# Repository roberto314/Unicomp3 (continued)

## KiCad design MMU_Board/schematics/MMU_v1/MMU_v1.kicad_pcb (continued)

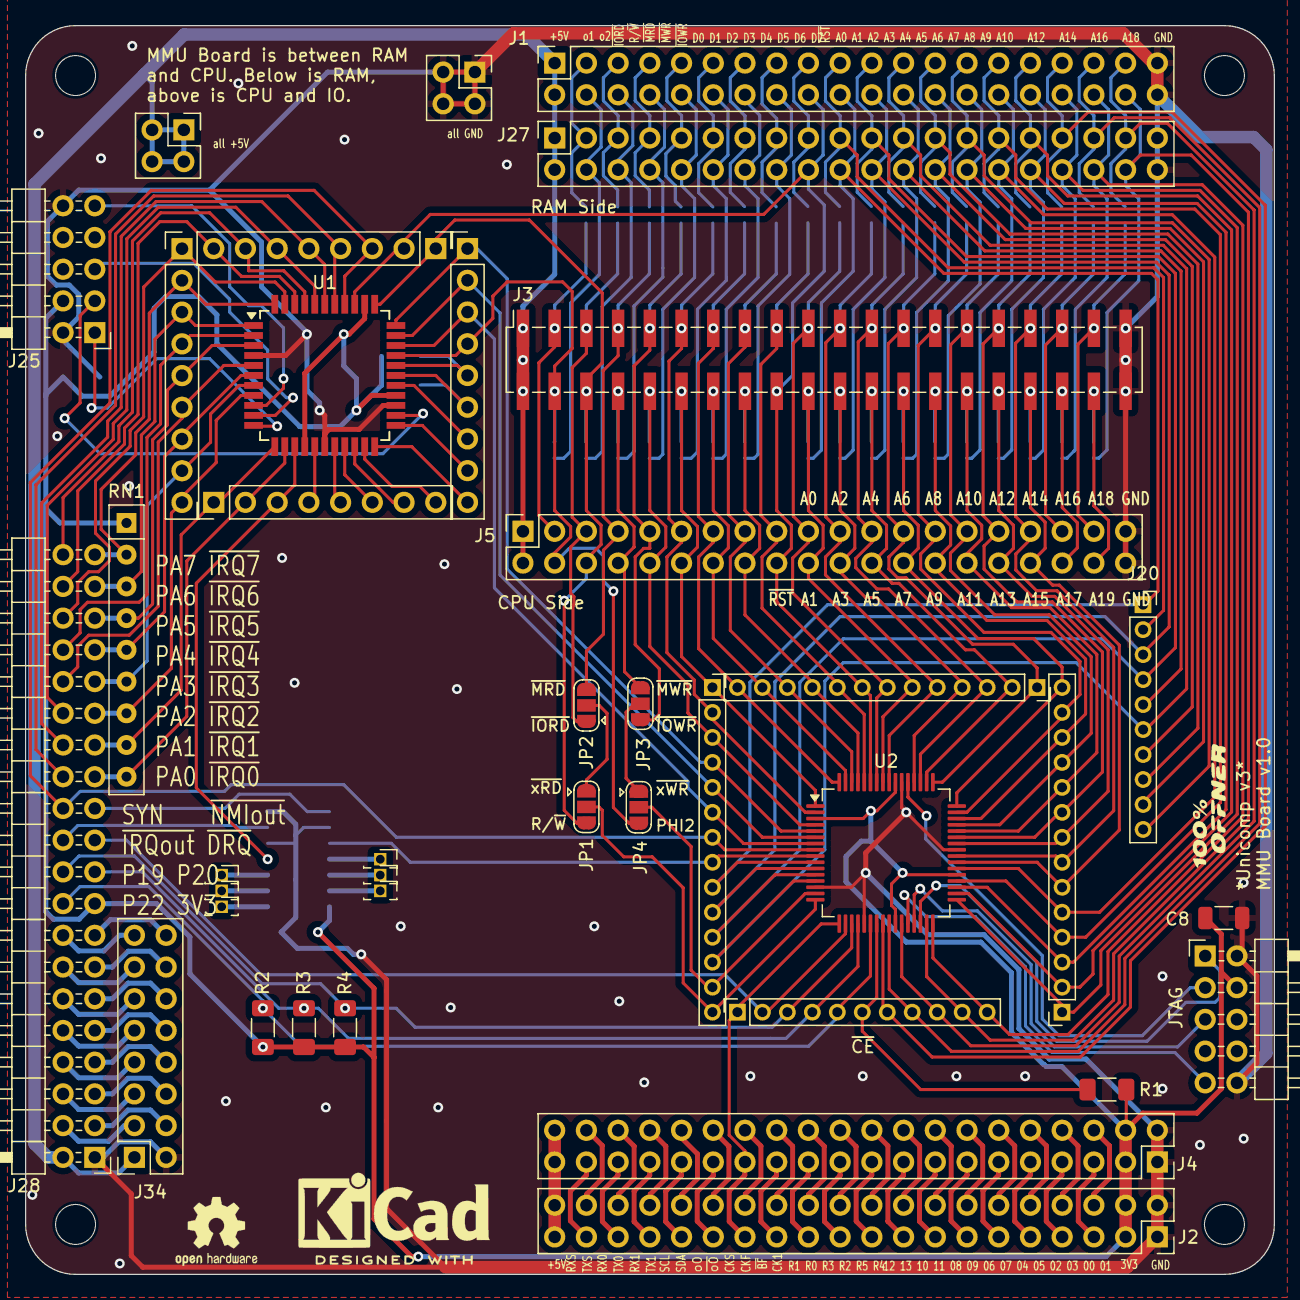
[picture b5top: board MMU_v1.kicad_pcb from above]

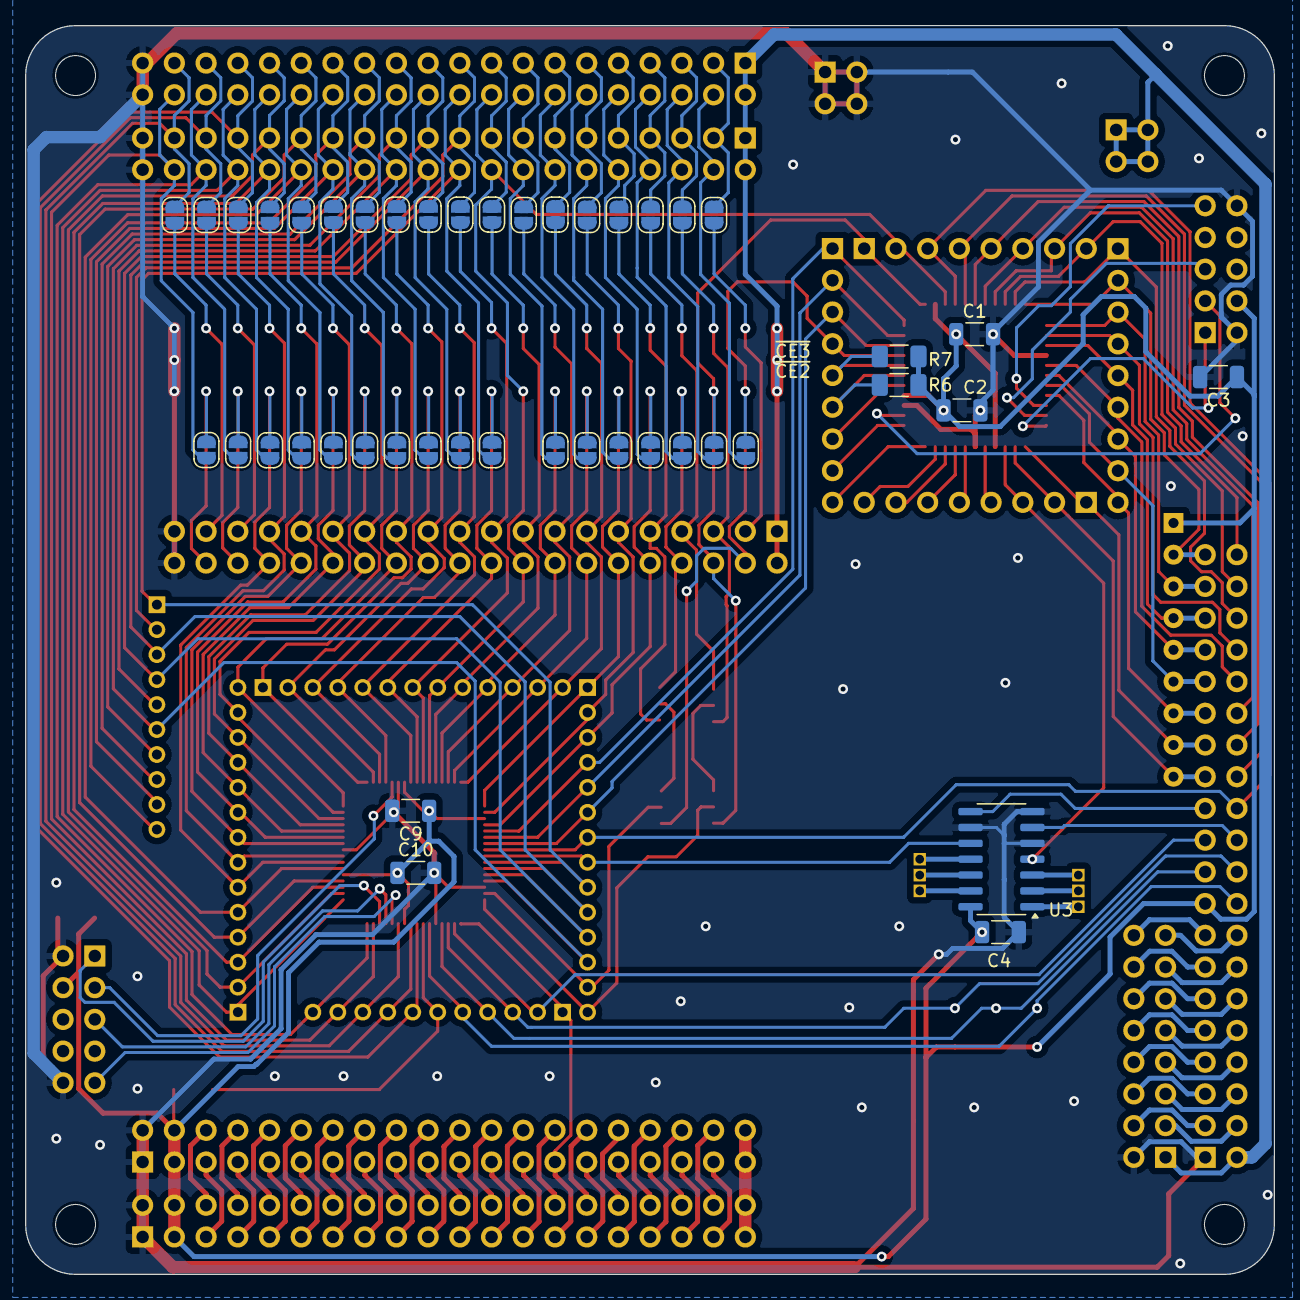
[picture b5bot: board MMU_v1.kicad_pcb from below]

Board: 2 copper layers, 100.0 x 100.0 mm, 89 parts (44 on the bottom side), 180 nets.

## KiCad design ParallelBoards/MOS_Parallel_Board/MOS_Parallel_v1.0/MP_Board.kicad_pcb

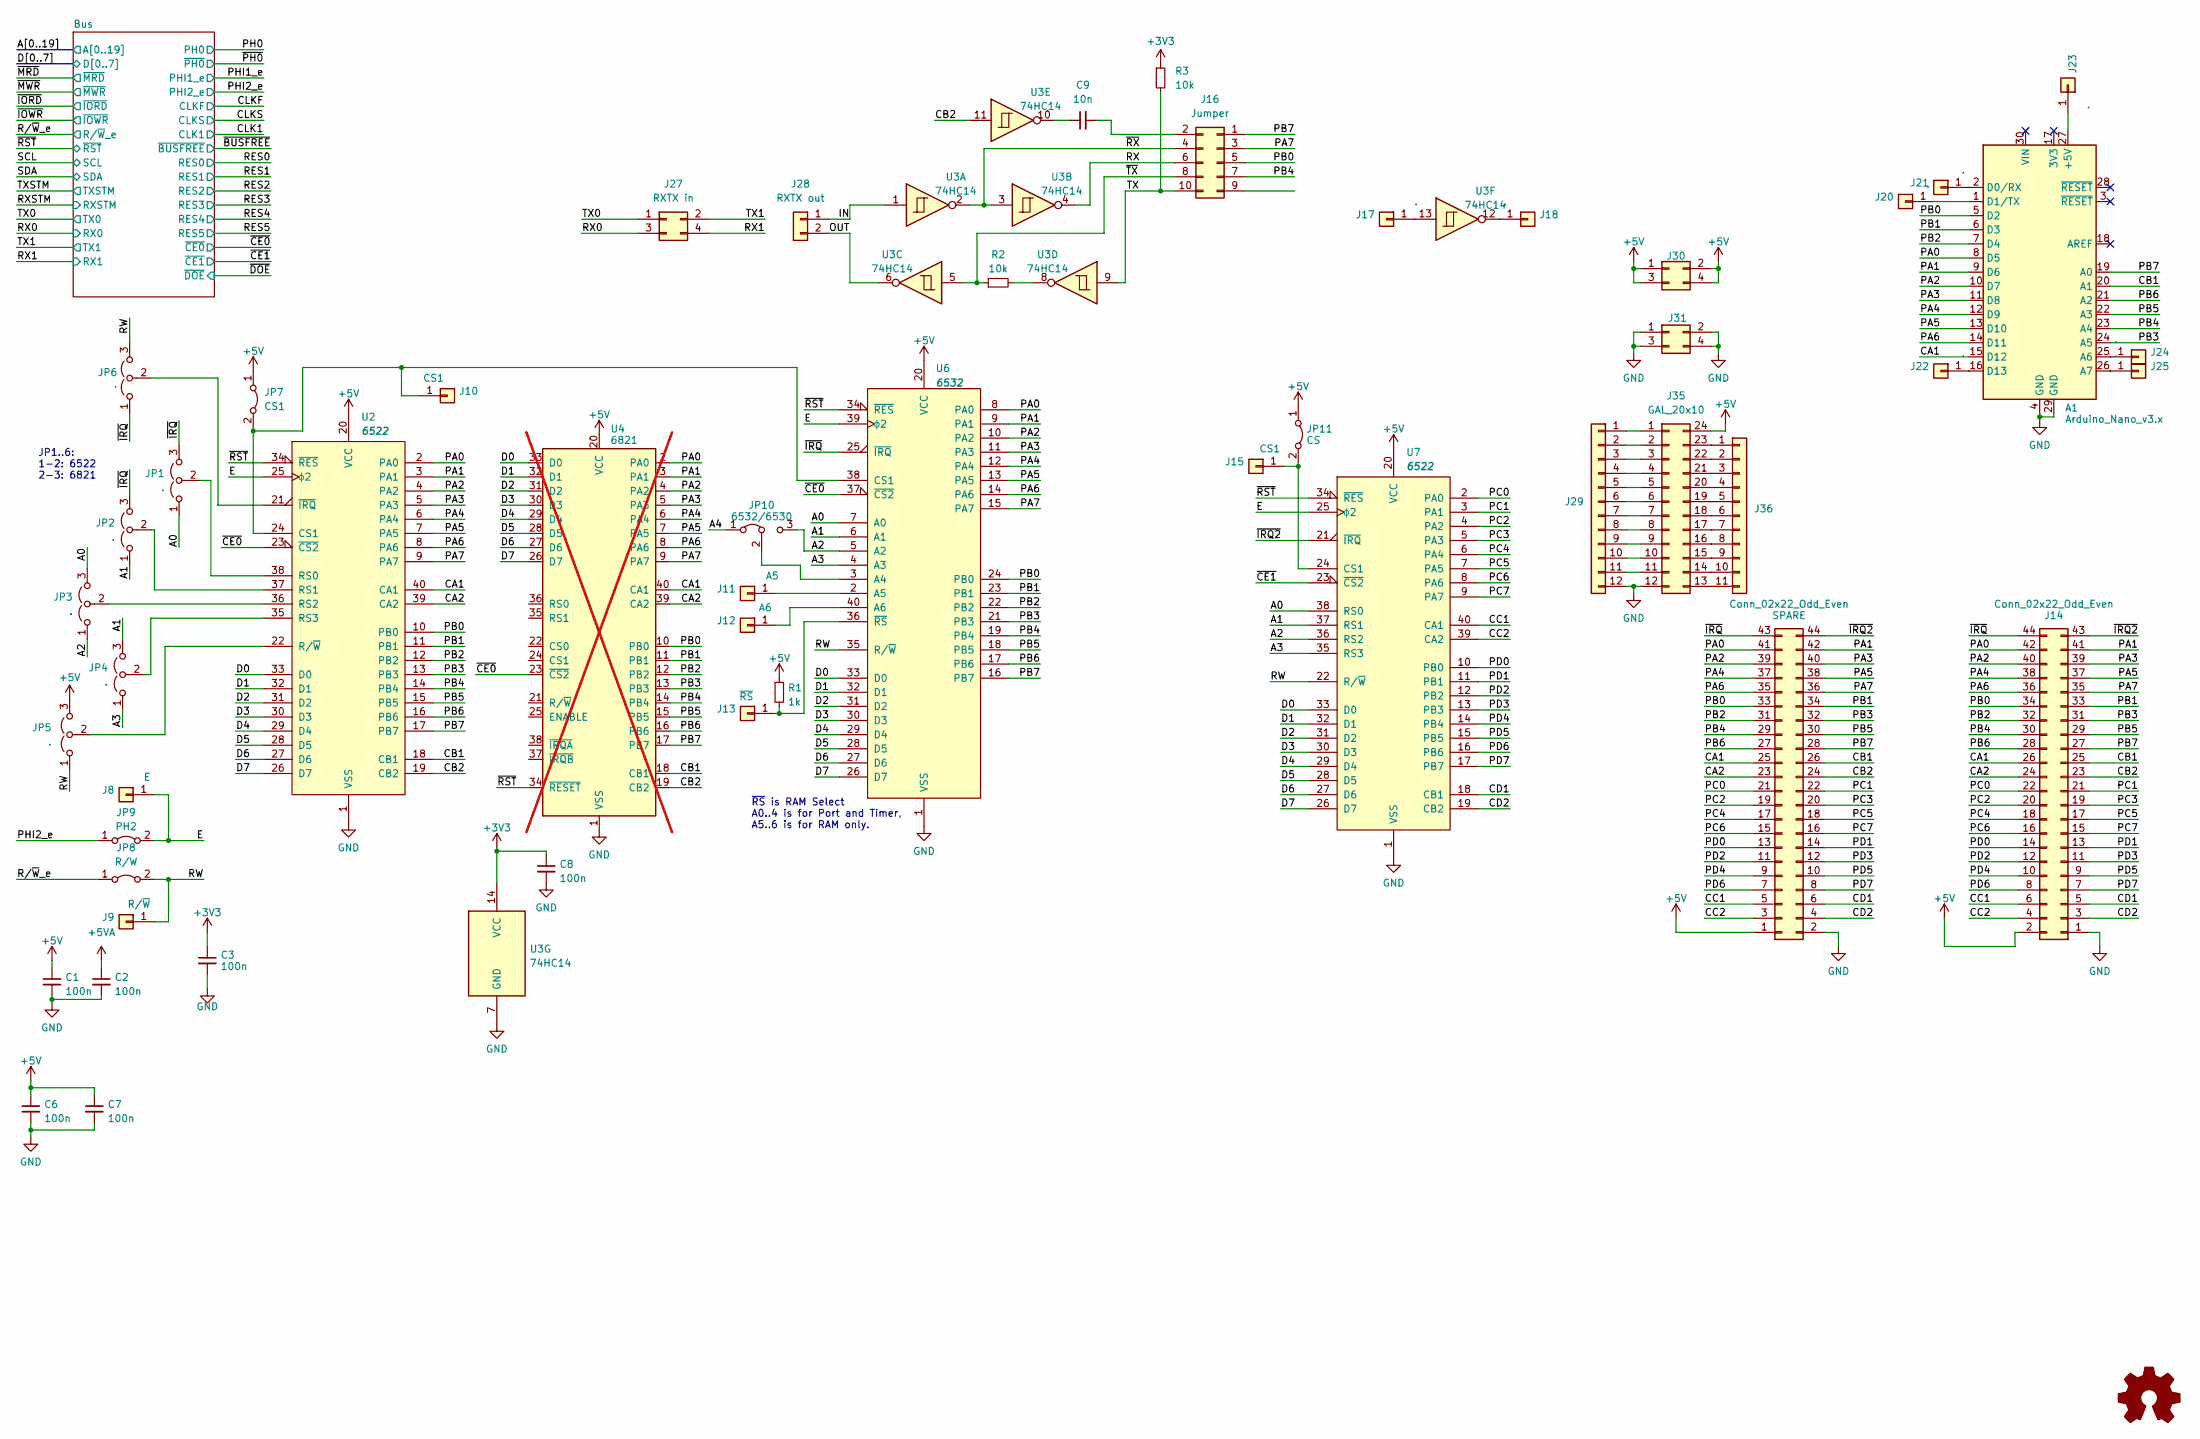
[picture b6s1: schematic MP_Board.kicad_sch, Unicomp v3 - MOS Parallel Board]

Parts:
A1: Arduino_Nano_v3.x; Arduino_Nano
C1, C2, C3, C6, C7, C8: 100n; C_1206_3216Metric
C9: 10n; C_1206_3216Metric
J8: E; PinHeader_1x01_P2.00mm_Vertical
J9: R/~{W}; PinHeader_1x01_P2.00mm_Vertical
J10, J15: CS1; PinHeader_1x01_P2.00mm_Vertical
J11: A5; PinHeader_1x01_P2.00mm_Vertical
J12: A6; PinHeader_1x01_P2.00mm_Vertical
J13: ~{RS}; PinHeader_1x01_P2.00mm_Vertical
J14: Conn_02x22_Odd_Even; PinHeader_2x22_P2.54mm_Horizontal
J16: Jumper; PinSocket_2x05_P2.54mm_Vertical
J17, J18, J20, J21, J22, J23, J24, J25: .; PinHeader_1x01_P2.00mm_Vertical
J27: RXTX in; PinSocket_2x02_P2.54mm_Vertical
J28: RXTX out; PinSocket_1x02_P2.54mm_Vertical
J29: Conn_01x12; PinSocket_1x12_P2.54mm_Vertical
J30, J31: Conn_02x02_Odd_Even; PinSocket_2x02_P2.54mm_Vertical
J35: GAL_20x10; DIP-24_W7.62mm
J36: Conn_01x11; PinSocket_1x11_P2.54mm_Vertical
JP1, JP2, JP3, JP4, JP5, JP6: .; PinHeader_1x03_P2.54mm_Vertical
JP7: CS1; SolderJumper-2_P1.3mm_Bridged_RoundedPad1.0x1.5mm
JP8: R/W; SolderJumper-2_P1.3mm_Bridged_RoundedPad1.0x1.5mm
JP9: PH2; SolderJumper-2_P1.3mm_Bridged_RoundedPad1.0x1.5mm
JP10: 6532/6530; SolderJumper-3_P1.3mm_Bridged12_Pad1.0x1.5mm_NumberLabels
JP11: CS; SolderJumper-2_P1.3mm_Bridged_RoundedPad1.0x1.5mm
R1: 1k; R_1206_3216Metric_Pad1.30x1.75mm_HandSolder
R2, R3: 10k; R_1206_3216Metric_Pad1.30x1.75mm_HandSolder
SPARE: Conn_02x22_Odd_Even; PinSocket_2x22_P2.54mm_Vertical
U2, U7: 6522; DIP-40_W15.24mm_Socket
U3: 74HC14; SOIC-14_3.9x8.7mm_P1.27mm
U4: 6821; DIP-40_W15.24mm; not fitted
U6: 6532; DIP-40_W15.24mm_Socket

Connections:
+3V3: C3.1, C8.1, R3.1, U3.14 (VCC); also elsewhere on the board
+5V: C1.1, C6.1, C7.1, J14.2, J30.1, J30.2, J30.3, J30.4, J35.24, JP5.3 (B), JP7.1 (A), JP11.1 (A), R1.1, SPARE.1, U2.20 (VCC), U4.20 (VCC), U6.20 (VCC), U7.20 (VCC); also elsewhere on the board
+5VA: C2.1; also elsewhere on the board
/A0: JP1.1 (A), JP3.3 (B), U6.7 (A0), U7.38 (RS0); also elsewhere on the board
/A1: JP2.1 (A), JP4.3 (B), U6.6 (A1), U7.37 (RS1); also elsewhere on the board
/A2: JP3.1 (A), JP10.3 (B), U6.5 (A2), U7.36 (RS2); also elsewhere on the board
/A3: JP4.1 (A), U6.4 (A3), U7.35 (RS3); also elsewhere on the board
/A4: JP10.1 (A); also elsewhere on the board
/CA1: A1.15 (D12), J14.26, SPARE.25, U2.40 (CA1), U4.40 (CA1); also elsewhere on the board
/CA2: J14.24, SPARE.23, U2.39 (CA2), U4.39 (CA2); also elsewhere on the board
/CB1: A1.20 (A1), J14.25, SPARE.26, U2.18 (CB1), U4.18 (CB1); also elsewhere on the board
/CB2: J14.23, SPARE.24, U2.19 (CB2), U3.11, U4.19 (CB2); also elsewhere on the board
/CC1: J14.6, SPARE.5, U7.40 (CA1); also elsewhere on the board
/CC2: J14.4, SPARE.3, U7.39 (CA2); also elsewhere on the board
/CD1: J14.5, SPARE.6, U7.18 (CB1); also elsewhere on the board
/CD2: J14.3, SPARE.4, U7.19 (CB2); also elsewhere on the board
/D0: U2.33 (D0), U4.33 (D0), U6.33 (D0), U7.33 (D0); also elsewhere on the board
/D1: U2.32 (D1), U4.32 (D1), U6.32 (D1), U7.32 (D1); also elsewhere on the board
/D2: U2.31 (D2), U4.31 (D2), U6.31 (D2), U7.31 (D2); also elsewhere on the board
/D3: U2.30 (D3), U4.30 (D3), U6.30 (D3), U7.30 (D3); also elsewhere on the board
/D4: U2.29 (D4), U4.29 (D4), U6.29 (D4), U7.29 (D4); also elsewhere on the board
/D5: U2.28 (D5), U4.28 (D5), U6.28 (D5), U7.28 (D5); also elsewhere on the board
/D6: U2.27 (D6), U4.27 (D6), U6.27 (D6), U7.27 (D6); also elsewhere on the board
/D7: U2.26 (D7), U4.26 (D7), U6.26 (D7), U7.26 (D7); also elsewhere on the board
/E: J8.1, JP9.2 (B), U2.25 (ϕ2), U6.39 (ϕ2), U7.25 (ϕ2)
/IN: J28.1, U3.1
/OUT: J28.2, U3.6
/PA0: A1.8 (D5), J14.42, SPARE.41, U2.2 (PA0), U4.2 (PA0), U6.8 (PA0); also elsewhere on the board
/PA1: A1.9 (D6), J14.41, SPARE.42, U2.3 (PA1), U4.3 (PA1), U6.9 (PA1); also elsewhere on the board
/PA2: A1.10 (D7), J14.40, SPARE.39, U2.4 (PA2), U4.4 (PA2), U6.10 (PA2); also elsewhere on the board
/PA3: A1.11 (D8), J14.39, SPARE.40, U2.5 (PA3), U4.5 (PA3), U6.11 (PA3); also elsewhere on the board
/PA4: A1.12 (D9), J14.38, SPARE.37, U2.6 (PA4), U4.6 (PA4), U6.12 (PA4); also elsewhere on the board
/PA5: A1.13 (D10), J14.37, SPARE.38, U2.7 (PA5), U4.7 (PA5), U6.13 (PA5); also elsewhere on the board
/PA6: A1.14 (D11), J14.36, SPARE.35, U2.8 (PA6), U4.8 (PA6), U6.14 (PA6); also elsewhere on the board
/PA7: J14.35, J16.3, SPARE.36, U2.9 (PA7), U4.9 (PA7), U6.15 (PA7); also elsewhere on the board
/PB0: A1.5 (D2), J14.34, J16.5, SPARE.33, U2.10 (PB0), U4.10 (PB0), U6.24 (PB0); also elsewhere on the board
/PB1: A1.6 (D3), J14.33, SPARE.34, U2.11 (PB1), U4.11 (PB1), U6.23 (PB1); also elsewhere on the board
/PB2: A1.7 (D4), J14.32, SPARE.31, U2.12 (PB2), U4.12 (PB2), U6.22 (PB2); also elsewhere on the board
/PB3: A1.24 (A5), J14.31, SPARE.32, U2.13 (PB3), U4.13 (PB3), U6.21 (PB3); also elsewhere on the board
/PB4: A1.23 (A4), J14.30, J16.7, SPARE.29, U2.14 (PB4), U4.14 (PB4), U6.19 (PB4); also elsewhere on the board
/PB5: A1.22 (A3), J14.29, SPARE.30, U2.15 (PB5), U4.15 (PB5), U6.18 (PB5); also elsewhere on the board
/PB6: A1.21 (A2), J14.28, SPARE.27, U2.16 (PB6), U4.16 (PB6), U6.17 (PB6); also elsewhere on the board
/PB7: A1.19 (A0), J14.27, J16.1, SPARE.28, U2.17 (PB7), U4.17 (PB7), U6.16 (PB7); also elsewhere on the board
/PC0: J14.22, SPARE.21, U7.2 (PA0); also elsewhere on the board
/PC1: J14.21, SPARE.22, U7.3 (PA1); also elsewhere on the board
/PC2: J14.20, SPARE.19, U7.4 (PA2); also elsewhere on the board
/PC3: J14.19, SPARE.20, U7.5 (PA3); also elsewhere on the board
/PC4: J14.18, SPARE.17, U7.6 (PA4); also elsewhere on the board
/PC5: J14.17, SPARE.18, U7.7 (PA5); also elsewhere on the board
/PC6: J14.16, SPARE.15, U7.8 (PA6); also elsewhere on the board
/PC7: J14.15, SPARE.16, U7.9 (PA7); also elsewhere on the board
/PD0: J14.14, SPARE.13, U7.10 (PB0); also elsewhere on the board
/PD1: J14.13, SPARE.14, U7.11 (PB1); also elsewhere on the board
/PD2: J14.12, SPARE.11, U7.12 (PB2); also elsewhere on the board
/PD3: J14.11, SPARE.12, U7.13 (PB3); also elsewhere on the board
/PD4: J14.10, SPARE.9, U7.14 (PB4); also elsewhere on the board
/PD5: J14.9, SPARE.10, U7.15 (PB5); also elsewhere on the board
/PD6: J14.8, SPARE.7, U7.16 (PB6); also elsewhere on the board
/PD7: J14.7, SPARE.8, U7.17 (PB7); also elsewhere on the board
/PHI2_e: JP9.1 (A); also elsewhere on the board
/RW: J9.1, JP5.1 (A), JP6.3 (B), JP8.2 (B), U6.35 (R/~W), U7.22 (R/~W)
/RX: J16.6, U3.4
/RX0: J27.3; also elsewhere on the board
/RX1: J27.4; also elsewhere on the board
/R/~W_e: JP8.1 (A); also elsewhere on the board
/TX: J16.10, R3.2, U3.9
/TX0: J27.1; also elsewhere on the board
/TX1: J27.2; also elsewhere on the board
/~CE0: U2.23 (~CS2), U4.23 (~CS2), U6.37 (~CS2); also elsewhere on the board
/~CE1: U7.23 (~CS2); also elsewhere on the board
/~IRQ2: J14.43, SPARE.44, U7.21 (~IRQ); also elsewhere on the board
/~IRQ: J14.44, JP1.3 (B), JP2.3 (B), JP6.1 (A), SPARE.43, U6.25 (~IRQ); also elsewhere on the board
/~RST: U2.34 (~RES), U4.34 (~RESET), U6.34 (~RES), U7.34 (~RES); also elsewhere on the board
/~RX: J16.4, U3.2, U3.3
/~TX: J16.8, R2.1, U3.5
GND: A1.4 (GND), A1.29 (GND), C1.2, C2.2, C3.2, C6.2, C7.2, C8.2, J14.1, J29.12, J31.1, J31.2, J31.3, J31.4, J35.12, SPARE.2, U2.1 (VSS), U3.7 (GND), U4.1 (VSS), U6.1 (VSS), U7.1 (VSS); also elsewhere on the board
unnamed: A1.27 (+5V), J23.1
unnamed: A1.25 (A6), J24.1
unnamed: A1.26 (A7), J25.1
unnamed: A1.2 (D0/RX), J21.1
unnamed: A1.1 (D1/TX), J20.1
unnamed: A1.16 (D13), J22.1
unnamed: C9.1, U3.10
unnamed: J10.1, JP7.2 (B), U2.24 (CS1), U6.38 (CS1)
unnamed: J11.1, U6.2 (A5)
unnamed: J12.1, U6.40 (A6)
unnamed: J13.1, R1.2, U6.36 (~RS)
unnamed: J15.1, JP11.2 (B), U7.24 (CS1)
unnamed: C9.2, J16.2
unnamed: J17.1, U3.13
unnamed: J18.1, U3.12
unnamed: J29.1, J35.1
unnamed: J29.2, J35.2
unnamed: J29.3, J35.3
unnamed: J29.4, J35.4
unnamed: J29.5, J35.5
unnamed: J29.6, J35.6
unnamed: J29.7, J35.7
unnamed: J29.8, J35.8
unnamed: J29.9, J35.9
unnamed: J29.10, J35.10
unnamed: J29.11, J35.11
unnamed: J35.13, J36.11
unnamed: J35.14, J36.10
unnamed: J35.15, J36.9
unnamed: J35.16, J36.8
unnamed: J35.17, J36.7
unnamed: J35.18, J36.6
unnamed: J35.19, J36.5
unnamed: J35.20, J36.4
unnamed: J35.21, J36.3
unnamed: J35.22, J36.2
unnamed: J35.23, J36.1
unnamed: JP1.2 (C), U2.38 (RS0)
unnamed: JP2.2 (C), U2.37 (RS1)
unnamed: JP3.2 (C), U2.36 (RS2)
unnamed: JP4.2 (C), U2.35 (RS3)
unnamed: JP5.2 (C), U2.22 (R/~W)
unnamed: JP6.2 (C), U2.21 (~IRQ)
unnamed: JP10.2 (C), U6.3 (A4)
unnamed: R2.2, U3.8

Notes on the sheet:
~{RS} is RAM Select A0..4 is for Port and Timer, A5..6 is for RAM only.
JP1..6: 1-2: 6522 2-3: 6821

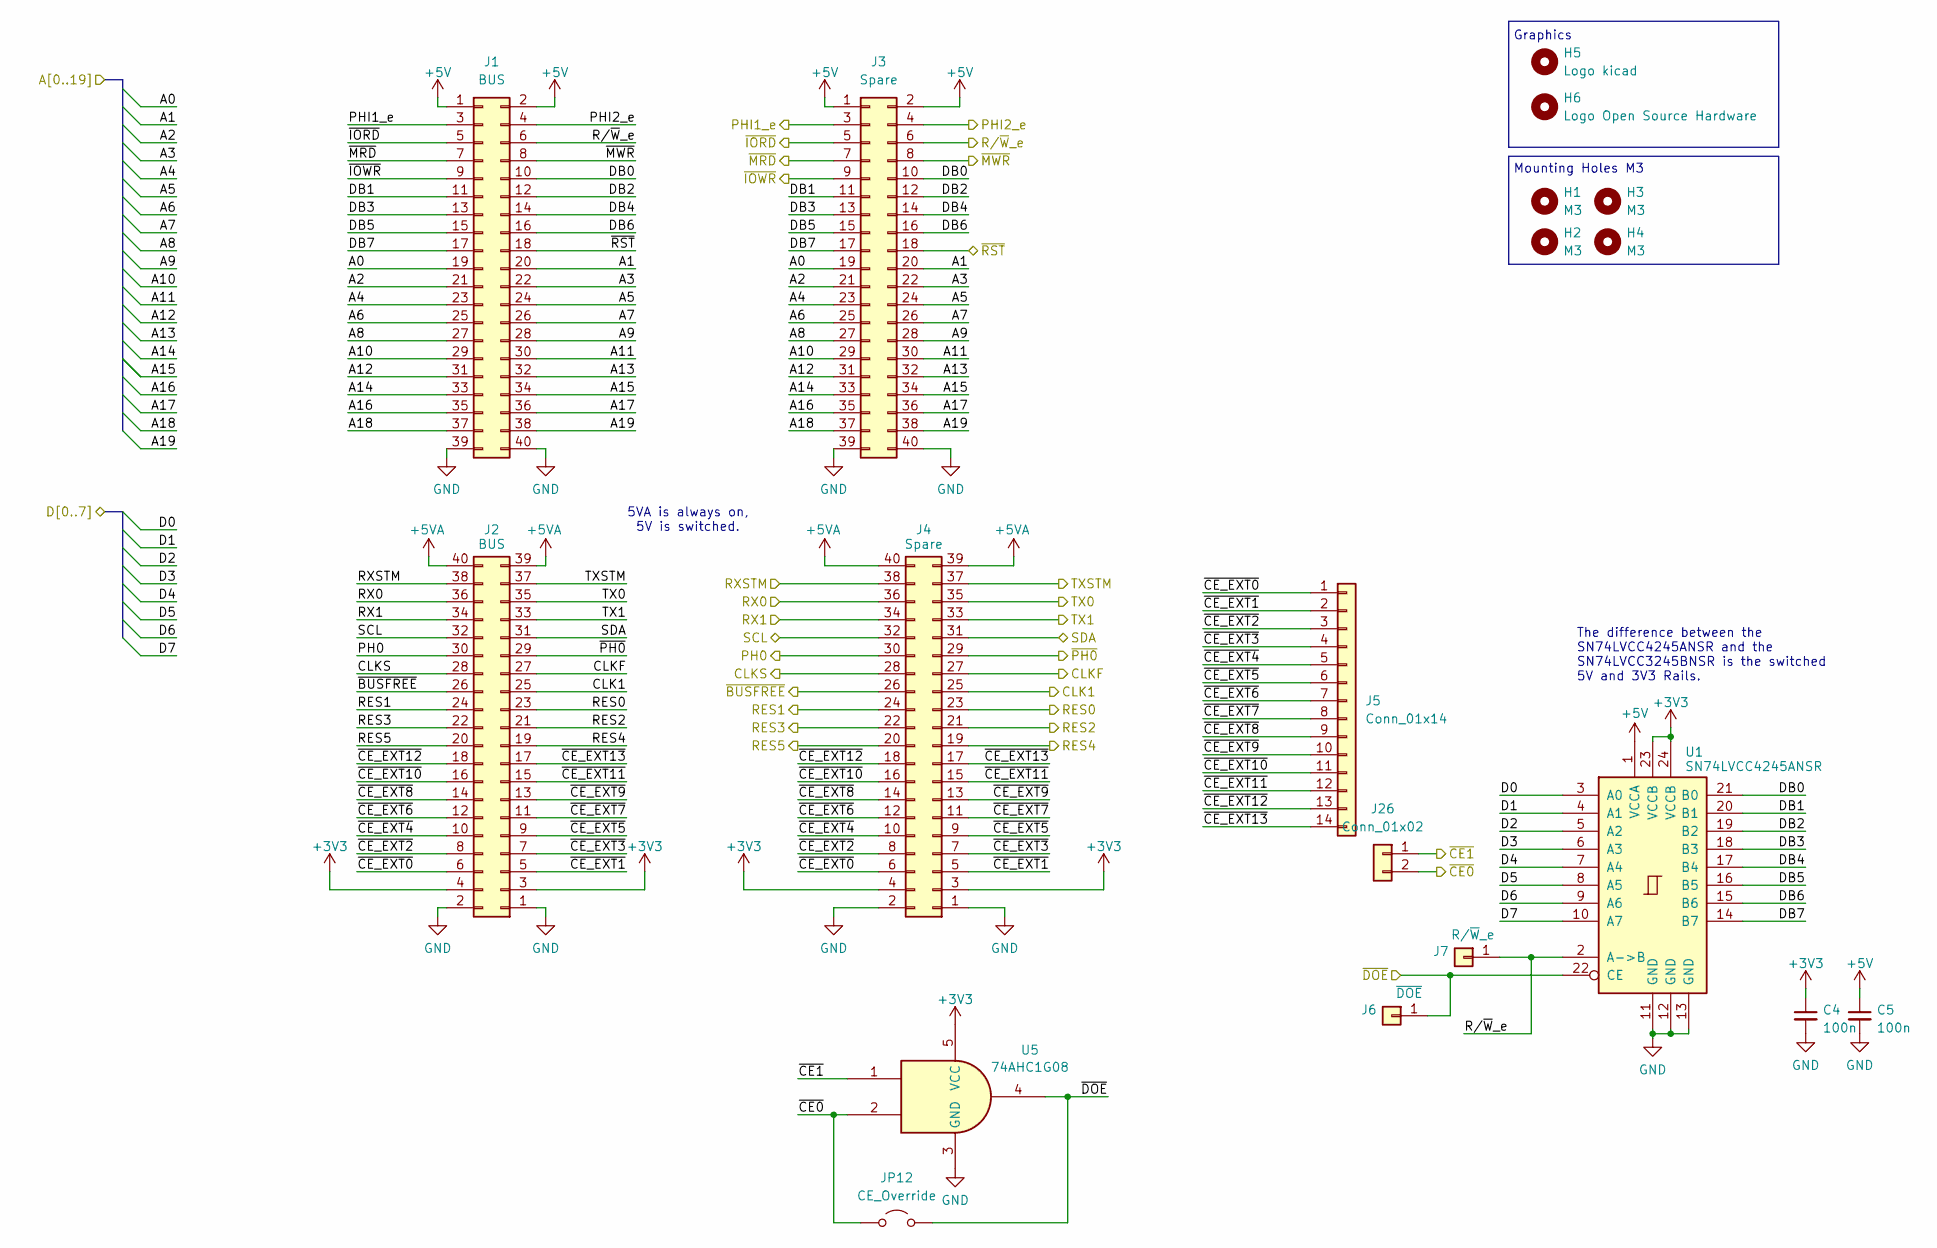
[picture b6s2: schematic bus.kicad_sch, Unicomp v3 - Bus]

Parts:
C4, C5: 100n; C_1206_3216Metric
H1, H2, H3, H4: M3; MountingHole_3.2mm_M3
H5: Logo kicad; KiCad-Logo2_6mm_SilkScreen
H6: Logo Open Source Hardware; OSHW-Logo2_7.3x6mm_SilkScreen
J1, J2: BUS; PinSocket_2x20_P2.54mm_Vertical
J3, J4: Spare; PinSocket_2x20_P2.54mm_Vertical
J5: Conn_01x14; PinSocket_1x14_P2.54mm_Vertical
J6: ~{DOE}; PinHeader_1x01_P2.00mm_Vertical
J7: R/~{W}_e; PinHeader_1x01_P2.00mm_Vertical
J26: Conn_01x02; PinSocket_1x02_P2.54mm_Vertical
JP12: CE_Override; SolderJumper-2_P1.3mm_Open_RoundedPad1.0x1.5mm
U1: SN74LVCC4245ANSR; SO-24_5.3x15mm_P1.27mm
U5: 74AHC1G08; SOT-23-5_HandSoldering

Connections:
+3V3: C4.1, J2.3, J2.4, J4.3, J4.4, U1.23 (VCCB), U1.24 (VCCB), U5.5 (VCC); also elsewhere on the board
+5V: C5.1, J1.1, J1.2, J3.1, J3.2, U1.1 (VCCA); also elsewhere on the board
+5VA: J2.39, J2.40, J4.39, J4.40; also elsewhere on the board
/A0: J1.19, J3.19; also elsewhere on the board
/A1: J1.20, J3.20; also elsewhere on the board
/A2: J1.21, J3.21; also elsewhere on the board
/A3: J1.22, J3.22; also elsewhere on the board
/A4: J1.23, J3.23; also elsewhere on the board
/A5: J1.24, J3.24
/A6: J1.25, J3.25
/A7: J1.26, J3.26
/A8: J1.27, J3.27
/A9: J1.28, J3.28
/A10: J1.29, J3.29
/A11: J1.30, J3.30
/A12: J1.31, J3.31
/A13: J1.32, J3.32
/A14: J1.33, J3.33
/A15: J1.34, J3.34
/A16: J1.35, J3.35
/A17: J1.36, J3.36
/A18: J1.37, J3.37
/A19: J1.38, J3.38
/Bus/DB0: J1.10, J3.10, U1.21 (B0)
/Bus/DB1: J1.11, J3.11, U1.20 (B1)
/Bus/DB2: J1.12, J3.12, U1.19 (B2)
/Bus/DB3: J1.13, J3.13, U1.18 (B3)
/Bus/DB4: J1.14, J3.14, U1.17 (B4)
/Bus/DB5: J1.15, J3.15, U1.16 (B5)
/Bus/DB6: J1.16, J3.16, U1.15 (B6)
/Bus/DB7: J1.17, J3.17, U1.14 (B7)
/Bus/~CE_EXT0: J2.6, J4.6, J5.1
/Bus/~CE_EXT1: J2.5, J4.5, J5.2
/Bus/~CE_EXT2: J2.8, J4.8, J5.3
/Bus/~CE_EXT3: J2.7, J4.7, J5.4
/Bus/~CE_EXT4: J2.10, J4.10, J5.5
/Bus/~CE_EXT5: J2.9, J4.9, J5.6
/Bus/~CE_EXT6: J2.12, J4.12, J5.7
/Bus/~CE_EXT7: J2.11, J4.11, J5.8
/Bus/~CE_EXT8: J2.14, J4.14, J5.9
/Bus/~CE_EXT9: J2.13, J4.13, J5.10
/Bus/~CE_EXT10: J2.16, J4.16, J5.11
/Bus/~CE_EXT11: J2.15, J4.15, J5.12
/Bus/~CE_EXT12: J2.18, J4.18, J5.13
/Bus/~CE_EXT13: J2.17, J4.17, J5.14
/CLK1: J2.25, J4.25
/CLKF: J2.27, J4.27
/CLKS: J2.28, J4.28
/D0: U1.3 (A0); also elsewhere on the board
/D1: U1.4 (A1); also elsewhere on the board
/D2: U1.5 (A2); also elsewhere on the board
/D3: U1.6 (A3); also elsewhere on the board
/D4: U1.7 (A4); also elsewhere on the board
/D5: U1.8 (A5); also elsewhere on the board
/D6: U1.9 (A6); also elsewhere on the board
/D7: U1.10 (A7); also elsewhere on the board
/PH0: J2.30, J4.30
/PHI1_e: J1.3, J3.3
/PHI2_e: J1.4, J3.4; also elsewhere on the board
/RES0: J2.23, J4.23
/RES1: J2.24, J4.24
/RES2: J2.21, J4.21
/RES3: J2.22, J4.22
/RES4: J2.19, J4.19
/RES5: J2.20, J4.20
/RX0: J2.36, J4.36; also elsewhere on the board
/RX1: J2.34, J4.34; also elsewhere on the board
/RXSTM: J2.38, J4.38
/R/~W_e: J1.6, J3.6, J7.1, U1.2 (A->B); also elsewhere on the board
/SCL: J2.32, J4.32
/SDA: J2.31, J4.31
/TX0: J2.35, J4.35; also elsewhere on the board
/TX1: J2.33, J4.33; also elsewhere on the board
/TXSTM: J2.37, J4.37
/~BUSFREE: J2.26, J4.26
/~CE0: J26.2, JP12.1 (A), U5.2; also elsewhere on the board
/~CE1: J26.1, U5.1; also elsewhere on the board
/~DOE: J6.1, JP12.2 (B), U1.22 (CE), U5.4
/~IORD: J1.5, J3.5
/~IOWR: J1.9, J3.9
/~MRD: J1.7, J3.7
/~MWR: J1.8, J3.8
/~PH0: J2.29, J4.29
/~RST: J1.18, J3.18; also elsewhere on the board
GND: C4.2, C5.2, J1.39, J1.40, J2.1, J2.2, J3.39, J3.40, J4.1, J4.2, U1.11 (GND), U1.12 (GND), U1.13 (GND), U5.3 (GND); also elsewhere on the board

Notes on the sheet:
Graphics
5VA is always on, 5V is switched.
Mounting Holes M3
The difference between the SN74LVCC4245ANSR and the SN74LVCC3245BNSR is the switched 5V and 3V3 Rails.

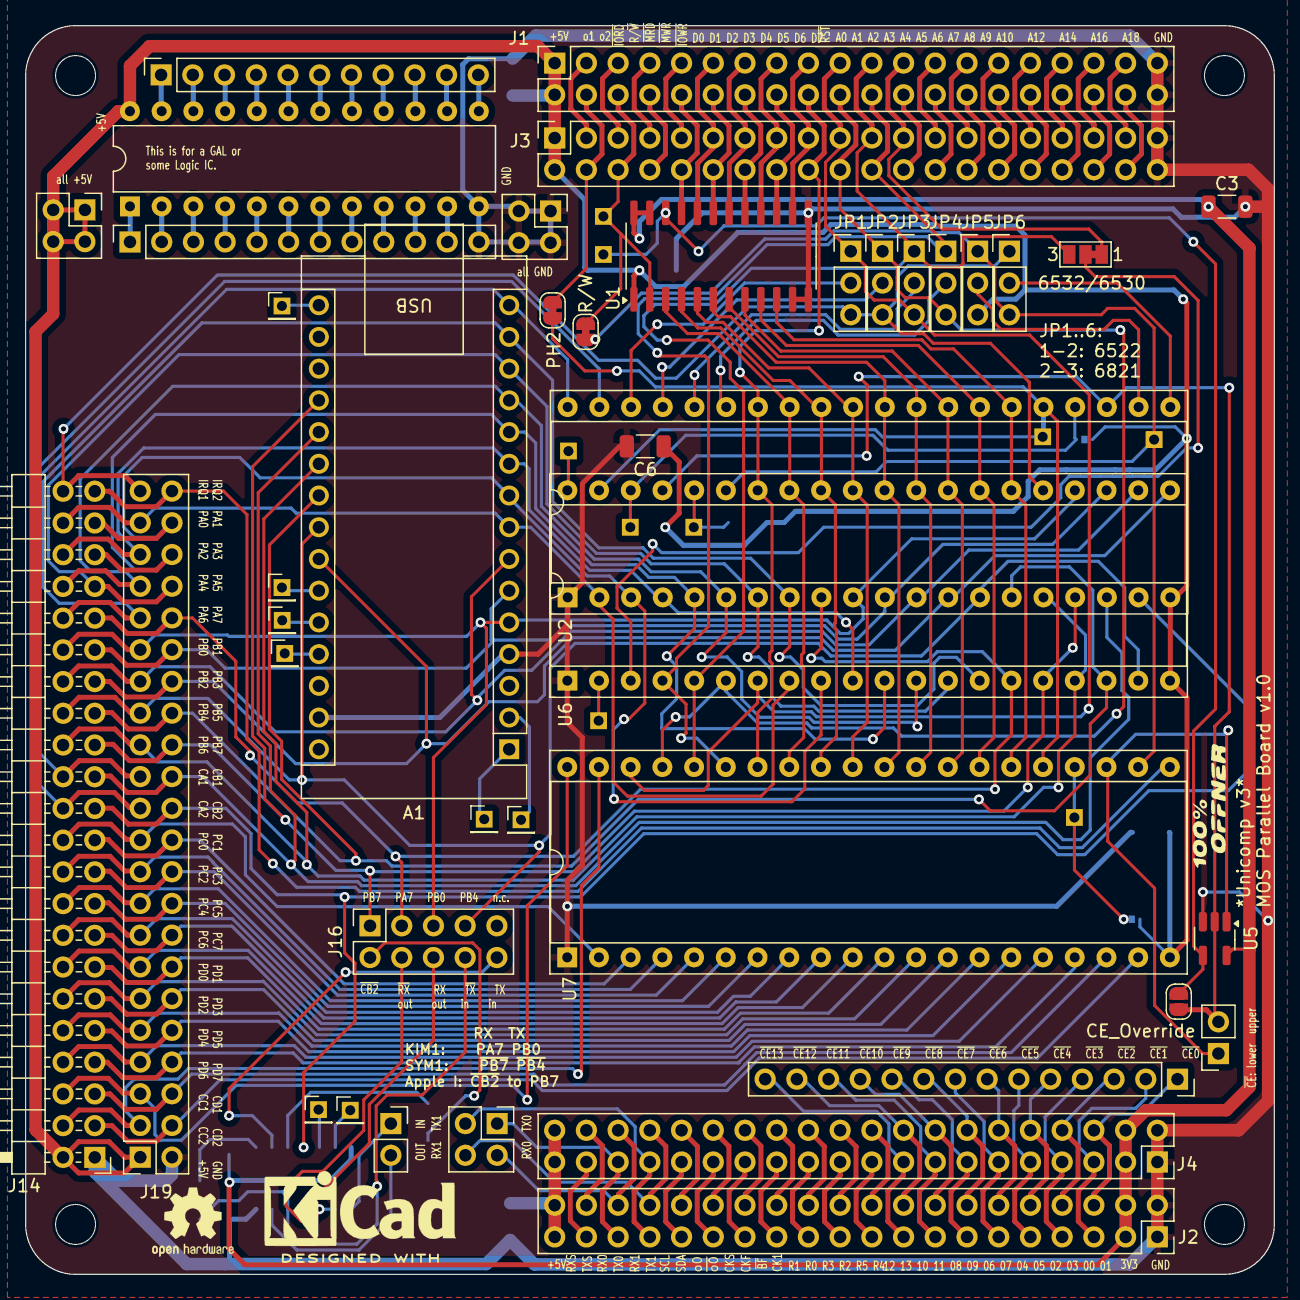
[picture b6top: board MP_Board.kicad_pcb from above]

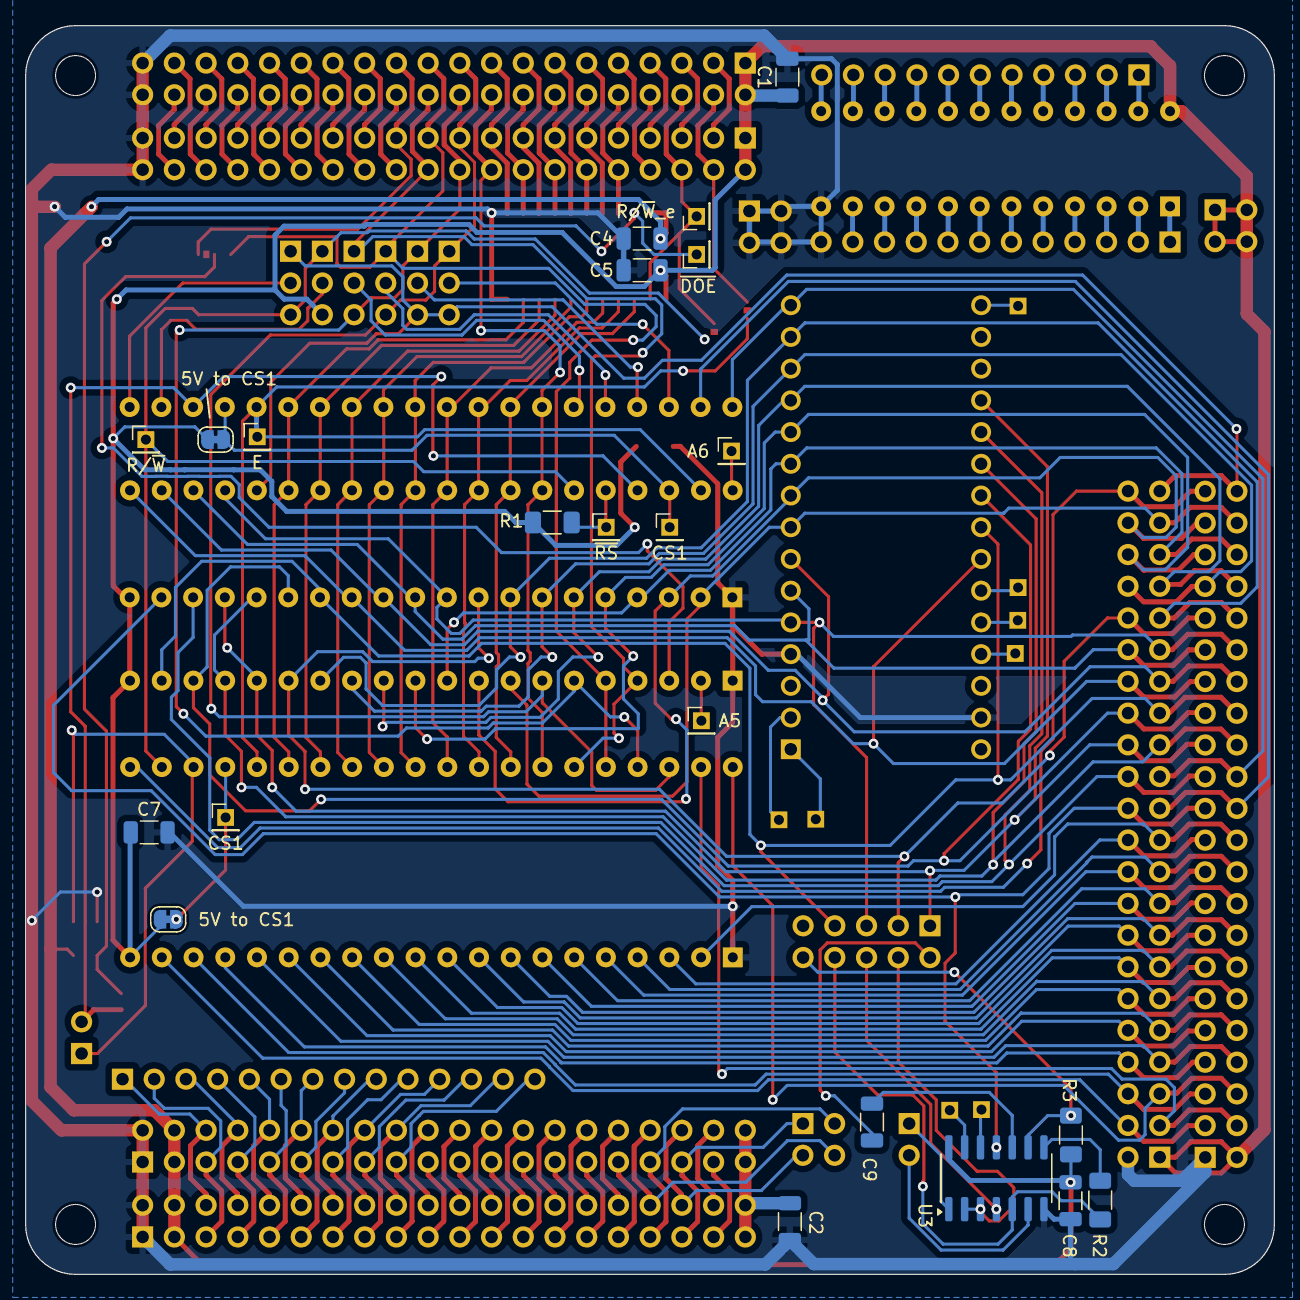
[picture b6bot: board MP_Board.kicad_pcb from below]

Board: 2 copper layers, 100.0 x 100.0 mm, 70 parts (22 on the bottom side), 180 nets.

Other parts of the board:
J19: Conn_02x22_Odd_Even; PinSocket_2x22_P2.54mm_Vertical

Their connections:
+5V: J19.1; also elsewhere on the board
/CA1: J19.25; also elsewhere on the board
/CA2: J19.23; also elsewhere on the board
/CB1: J19.26; also elsewhere on the board
/CB2: J19.24; also elsewhere on the board
/CC1: J19.5; also elsewhere on the board
/CC2: J19.3; also elsewhere on the board
/CD1: J19.6; also elsewhere on the board
/CD2: J19.4; also elsewhere on the board
/PA0: J19.41; also elsewhere on the board
/PA1: J19.42; also elsewhere on the board
/PA2: J19.39; also elsewhere on the board
/PA3: J19.40; also elsewhere on the board
/PA4: J19.37; also elsewhere on the board
/PA5: J19.38; also elsewhere on the board
/PA6: J19.35; also elsewhere on the board
/PA7: J19.36; also elsewhere on the board
/PB0: J19.33; also elsewhere on the board
/PB1: J19.34; also elsewhere on the board
/PB2: J19.31; also elsewhere on the board
/PB3: J19.32; also elsewhere on the board
/PB4: J19.29; also elsewhere on the board
/PB5: J19.30; also elsewhere on the board
/PB6: J19.27; also elsewhere on the board
/PB7: J19.28; also elsewhere on the board
/PC0: J19.21; also elsewhere on the board
/PC1: J19.22; also elsewhere on the board
/PC2: J19.19; also elsewhere on the board
/PC3: J19.20; also elsewhere on the board
/PC4: J19.17; also elsewhere on the board
/PC5: J19.18; also elsewhere on the board
/PC6: J19.15; also elsewhere on the board
/PC7: J19.16; also elsewhere on the board
/PD0: J19.13; also elsewhere on the board
/PD1: J19.14; also elsewhere on the board
/PD2: J19.11; also elsewhere on the board
/PD3: J19.12; also elsewhere on the board
/PD4: J19.9; also elsewhere on the board
/PD5: J19.10; also elsewhere on the board
/PD6: J19.7; also elsewhere on the board
/PD7: J19.8; also elsewhere on the board
/~IRQ2: J19.44; also elsewhere on the board
/~IRQ: J19.43; also elsewhere on the board
GND: J19.2; also elsewhere on the board
